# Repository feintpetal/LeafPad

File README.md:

## LeafPad
The LeafPad is a 11 key macropad with a rotary encoder, an OLED Display and uses KMK firmware
---------------------------------------------------------------------------------------------
## Features:
- 11 keys for macros
- One rotary encoder for volume control
- An oled screen for bongo cat (Cuz y not)
---------------------------------------------------------------------------------------------
## CAD Model:

Made with Fusion

---------------------------------------------------------------------------------------------
## PCB:

### Schematic: 

### PCB: 
---------------------------------------------------------------------------------------------
## Firmware:
This hackpad uses [KMK](github.com/KMKfw/kmk_firmware/) for everything
This includes:
 - 11 macro keys
 - A rotary encoder for volume control
 - And an oled screen
## BOM:
- 11x Cherry Mx Switches
- 11x DSA Keycaps
- 12x 1N4148 DO-35 Diodes
- 1x XIAO RP2040
- 1x Case
- 1x EC11 Rotary Encoder
- 1x 0.91" 128x32 OLED Display
- 4x M3x16mm screws
- 4x M3x5mx4mm heatset inserts

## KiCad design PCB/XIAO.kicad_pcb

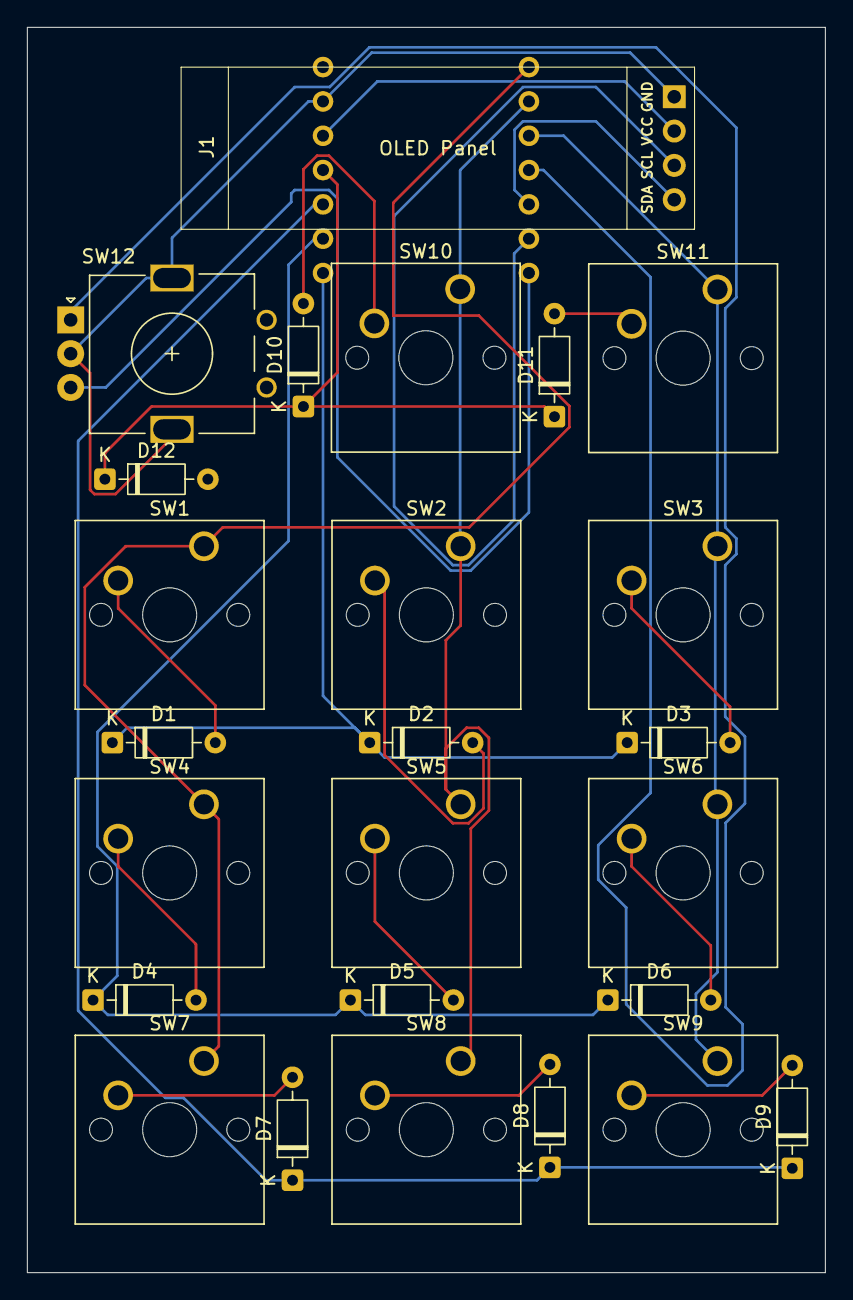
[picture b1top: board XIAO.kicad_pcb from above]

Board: 2 copper layers, 59.1 x 92.2 mm, 26 parts (1 on the bottom side), 24 nets.

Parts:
D1, D2, D3, D4, D5, D6, D7, D8, D9, D10, D11, D12: 1N4148; D_DO-35_SOD27_P7.62mm_Horizontal
J1: Conn_01x04_Pin; SSD1306-0.91-OLED-4pin-128x32
SW1, SW2, SW3, SW4, SW5, SW6, SW7, SW8, SW9, SW10, SW11: SW_Push; SW_Cherry_MX_1.00u_PCB
SW12: RotaryEncoder_Switch_MP; RotaryEncoder_Alps_EC11E_Vertical_H20mm
U1: XIAO-RP2040-DIP

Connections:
+3V3: J1.2, U1.12 (3V3)
C1: SW1.1, SW4.1, SW7.1, U1.1 (GPIO26/ADC0/A0)
C2: SW2.1, SW5.1, SW8.1, SW10.1, U1.2 (GPIO27/ADC1/A1)
C3: SW3.1, SW6.1, SW9.1, SW11.1, U1.3 (GPIO28/ADC2/A2)
GND: J1.1, SW12.C, SW12.MP, U1.13 (GND)
unnamed: D1.2 (A), SW1.2
unnamed: D2.2 (A), SW2.2
unnamed: D3.2 (A), SW3.2
unnamed: D4.2 (A), SW4.2
unnamed: D5.2 (A), SW5.2
unnamed: D6.2 (A), SW6.2
unnamed: D7.2 (A), SW7.2
unnamed: D8.2 (A), SW8.2
unnamed: D9.2 (A), SW9.2
unnamed: D10.2 (A), SW10.2
unnamed: D11.2 (A), SW11.2
R1: D1.1 (K), D2.1 (K), D3.1 (K), U1.8 (GPIO1/RX)
R2: D4.1 (K), D5.1 (K), D6.1 (K), U1.9 (GPIO2/SCK)
R3: D7.1 (K), D8.1 (K), D9.1 (K), U1.10 (GPIO4/MISO)
R4: D10.1 (K), D11.1 (K), D12.1 (K), U1.11 (GPIO3/MOSI)
SCL: J1.3, U1.6 (GPIO7/SCL)
SDA: J1.4, U1.5 (GPIO6/SDA)
SWa: SW12.A, U1.4 (GPIO29/ADC3/A3)
SWb: SW12.B, U1.7 (GPIO0/TX)

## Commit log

2026-03-28 LICENSE.md
2026-03-28 Create Cad
2026-04-02 Delete Production/gerbers.zip
    added the wrong file
